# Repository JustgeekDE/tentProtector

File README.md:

# tentProtector
A small led board you can attach to your tent pegs and lines, to prevent people from trippig over them

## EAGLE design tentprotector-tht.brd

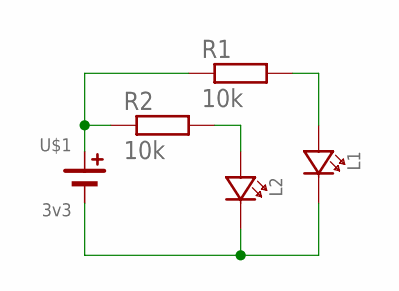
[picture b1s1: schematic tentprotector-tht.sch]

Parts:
L1, L2: LED5MM; LED-5MM
R1, R2: 10k; 0207/7
U$1: 3v3; BATTERY-CR2030-MIN

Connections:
+3V3: R1.1, R2.1, U$1.P$1 (PLUS), U$1.P$2 (PLUS)
GND: L1.K (C), L2.K (C), U$1.N$1 (MINUS)
unnamed: L1.A, R1.2
unnamed: L2.A, R2.2

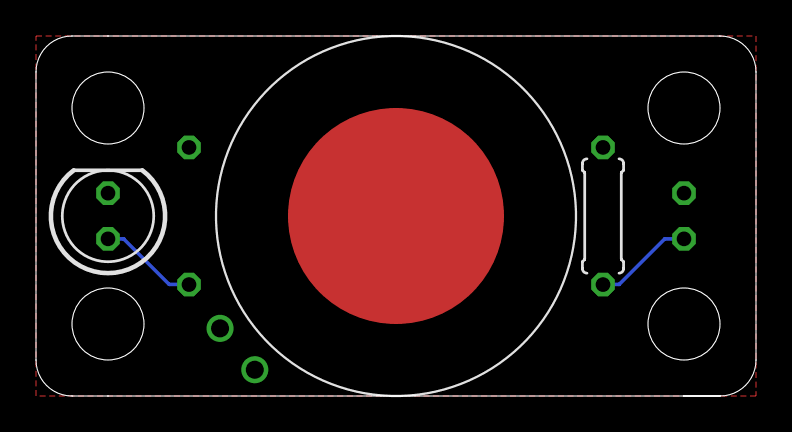
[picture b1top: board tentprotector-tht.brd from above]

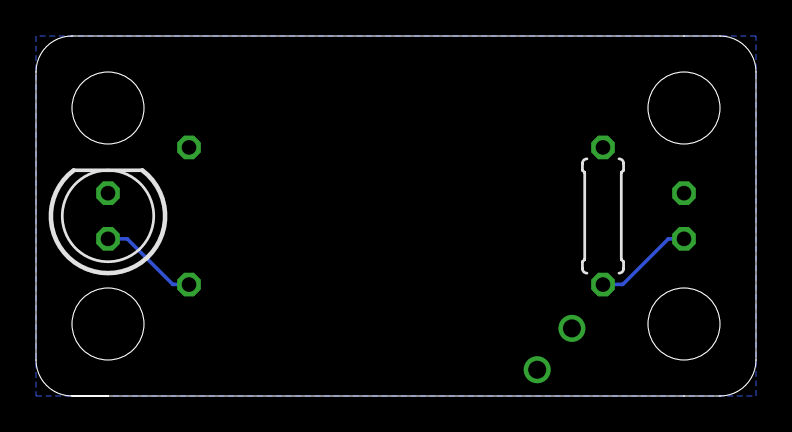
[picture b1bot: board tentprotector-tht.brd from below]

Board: 2 copper layers, 40.0 x 20.0 mm, 5 parts (2 on the bottom side), 4 nets.

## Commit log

2015-08-14 added license
2015-08-14 initial THT version
2015-08-14 added more variants
